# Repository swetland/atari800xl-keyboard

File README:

This is a work-in-progress replacement keyboard for the Atari800XL,
using Cherry MX mechanical key switches. 

- It is *not* entirely finished and production ready. 
- It has some clearance problems with the case top on the right hand side.  
- I do not have time to actively support it.

- Schematics and Layouts were done with KiCad 5.x

Parts Notes:
- A100254CT-ND (digikey) TE 2-84952-4 CONN FPC BOTTOM 24POS

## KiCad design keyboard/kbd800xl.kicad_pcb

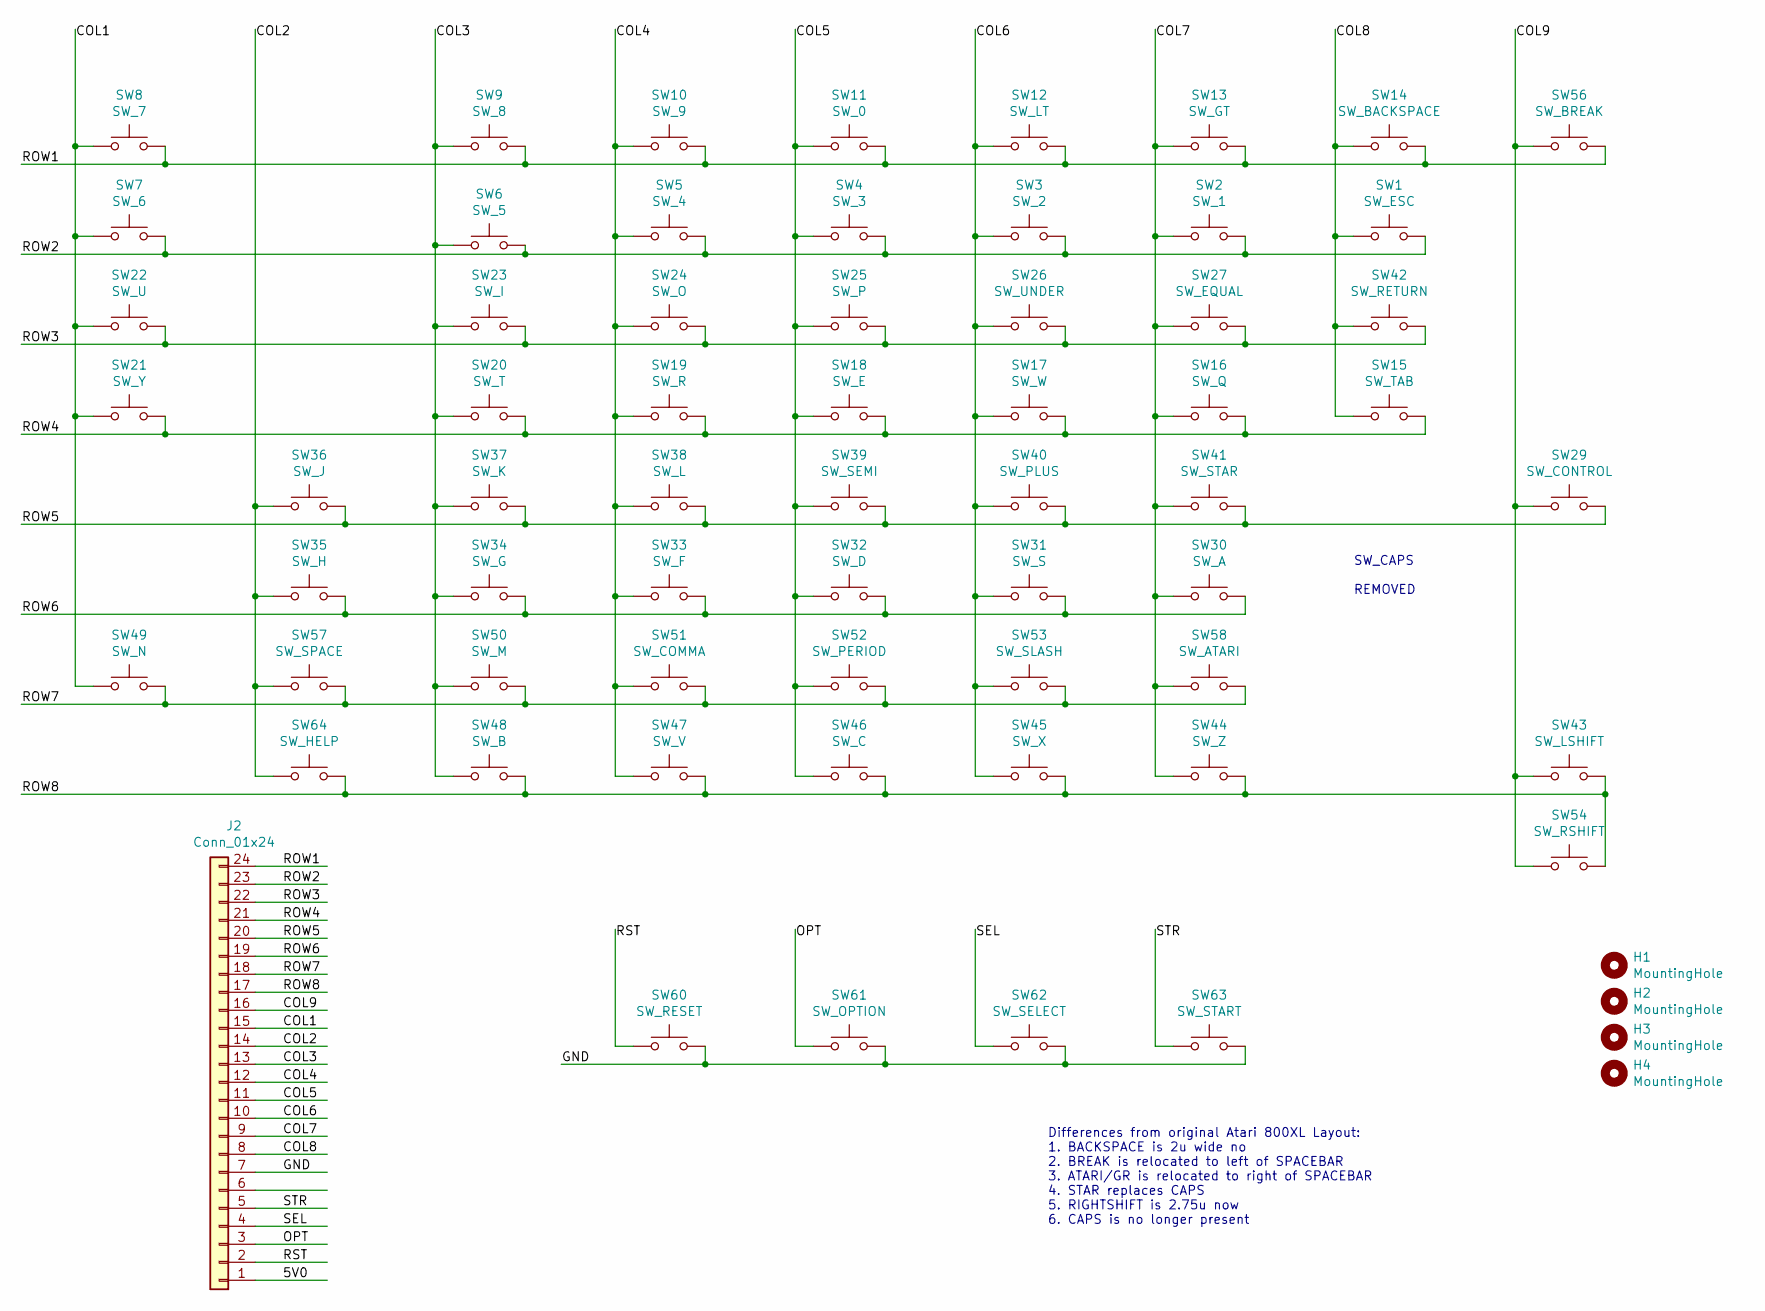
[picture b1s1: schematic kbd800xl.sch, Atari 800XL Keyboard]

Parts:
H1, H2, H3, H4: MountingHole; MountingHole_3mm
J2: Conn_01x24; TE_2-84952-4_1x24-1MP_P1.0mm_Horizontal
SW1: SW_ESC; SW_Cherry_MX_1.00u_PCB
SW2: SW_1; SW_Cherry_MX_1.00u_PCB
SW3: SW_2; SW_Cherry_MX_1.00u_PCB
SW4: SW_3; SW_Cherry_MX_1.00u_PCB
SW5: SW_4; SW_Cherry_MX_1.00u_PCB
SW6: SW_5; SW_Cherry_MX_1.00u_PCB
SW7: SW_6; SW_Cherry_MX_1.00u_PCB
SW8: SW_7; SW_Cherry_MX_1.00u_PCB
SW9: SW_8; SW_Cherry_MX_1.00u_PCB
SW10: SW_9; SW_Cherry_MX_1.00u_PCB
SW11: SW_0; SW_Cherry_MX_1.00u_PCB
SW12: SW_LT; SW_Cherry_MX_1.00u_PCB
SW13: SW_GT; SW_Cherry_MX_1.00u_PCB
SW14: SW_BACKSPACE; SW_Cherry_MX_2.00u_PCB
SW15: SW_TAB; SW_Cherry_MX_1.50u_PCB
SW16: SW_Q; SW_Cherry_MX_1.00u_PCB
SW17: SW_W; SW_Cherry_MX_1.00u_PCB
SW18: SW_E; SW_Cherry_MX_1.00u_PCB
SW19: SW_R; SW_Cherry_MX_1.00u_PCB
SW20: SW_T; SW_Cherry_MX_1.00u_PCB
SW21: SW_Y; SW_Cherry_MX_1.00u_PCB
SW22: SW_U; SW_Cherry_MX_1.00u_PCB
SW23: SW_I; SW_Cherry_MX_1.00u_PCB
SW24: SW_O; SW_Cherry_MX_1.00u_PCB
SW25: SW_P; SW_Cherry_MX_1.00u_PCB
SW26: SW_UNDER; SW_Cherry_MX_1.00u_PCB
SW27: SW_EQUAL; SW_Cherry_MX_1.00u_PCB
SW29: SW_CONTROL; SW_Cherry_MX_1.75u_PCB
SW30: SW_A; SW_Cherry_MX_1.00u_PCB
SW31: SW_S; SW_Cherry_MX_1.00u_PCB
SW32: SW_D; SW_Cherry_MX_1.00u_PCB
SW33: SW_F; SW_Cherry_MX_1.00u_PCB
SW34: SW_G; SW_Cherry_MX_1.00u_PCB
SW35: SW_H; SW_Cherry_MX_1.00u_PCB
SW36: SW_J; SW_Cherry_MX_1.00u_PCB
SW37: SW_K; SW_Cherry_MX_1.00u_PCB
SW38: SW_L; SW_Cherry_MX_1.00u_PCB
SW39: SW_SEMI; SW_Cherry_MX_1.00u_PCB
SW40: SW_PLUS; SW_Cherry_MX_1.00u_PCB
SW41: SW_STAR; SW_Cherry_MX_1.50u_PCB
SW42: SW_RETURN; SW_Cherry_MX_2.25u_PCB
SW43: SW_LSHIFT; SW_Cherry_MX_2.25u_PCB
SW44: SW_Z; SW_Cherry_MX_1.00u_PCB
SW45: SW_X; SW_Cherry_MX_1.00u_PCB
SW46: SW_C; SW_Cherry_MX_1.00u_PCB
SW47: SW_V; SW_Cherry_MX_1.00u_PCB
SW48: SW_B; SW_Cherry_MX_1.00u_PCB
SW49: SW_N; SW_Cherry_MX_1.00u_PCB
SW50: SW_M; SW_Cherry_MX_1.00u_PCB
SW51: SW_COMMA; SW_Cherry_MX_1.00u_PCB
SW52: SW_PERIOD; SW_Cherry_MX_1.00u_PCB
SW53: SW_SLASH; SW_Cherry_MX_1.00u_PCB
SW54: SW_RSHIFT; SW_Cherry_MX_2.75u_PCB
SW56: SW_BREAK; SW_Cherry_MX_1.25u_PCB
SW57: SW_SPACE; SW_Cherry_MX_6.25u_PCB
SW58: SW_ATARI; SW_Cherry_MX_1.25u_PCB
SW60: SW_RESET; SW_Cherry_MX_1.00u_PCB
SW61: SW_OPTION; SW_Cherry_MX_1.00u_PCB
SW62: SW_SELECT; SW_Cherry_MX_1.00u_PCB
SW63: SW_START; SW_Cherry_MX_1.00u_PCB
SW64: SW_HELP; SW_Cherry_MX_1.00u_PCB

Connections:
/5V0: J2.1
/COL1: J2.15, SW7.1, SW8.1, SW21.1, SW22.1, SW49.1
/COL2: J2.14, SW35.1, SW36.1, SW57.1, SW64.1
/COL3: J2.13, SW6.1, SW9.1, SW20.1, SW23.1, SW34.1, SW37.1, SW48.1, SW50.1
/COL4: J2.12, SW5.1, SW10.1, SW19.1, SW24.1, SW33.1, SW38.1, SW47.1, SW51.1
/COL5: J2.11, SW4.1, SW11.1, SW18.1, SW25.1, SW32.1, SW39.1, SW46.1, SW52.1
/COL6: J2.10, SW3.1, SW12.1, SW17.1, SW26.1, SW31.1, SW40.1, SW45.1, SW53.1
/COL7: J2.9, SW2.1, SW13.1, SW16.1, SW27.1, SW30.1, SW41.1, SW44.1, SW58.1
/COL8: J2.8, SW1.1, SW14.1, SW15.1, SW42.1
/COL9: J2.16, SW29.1, SW43.1, SW54.1, SW56.1
/GND: J2.7, SW60.2, SW61.2, SW62.2, SW63.2
/OPT: J2.3, SW61.1
/ROW1: J2.24, SW8.2, SW9.2, SW10.2, SW11.2, SW12.2, SW13.2, SW14.2, SW56.2
/ROW2: J2.23, SW1.2, SW2.2, SW3.2, SW4.2, SW5.2, SW6.2, SW7.2
/ROW3: J2.22, SW22.2, SW23.2, SW24.2, SW25.2, SW26.2, SW27.2, SW42.2
/ROW4: J2.21, SW15.2, SW16.2, SW17.2, SW18.2, SW19.2, SW20.2, SW21.2
/ROW5: J2.20, SW29.2, SW36.2, SW37.2, SW38.2, SW39.2, SW40.2, SW41.2
/ROW6: J2.19, SW30.2, SW31.2, SW32.2, SW33.2, SW34.2, SW35.2
/ROW7: J2.18, SW49.2, SW50.2, SW51.2, SW52.2, SW53.2, SW57.2, SW58.2
/ROW8: J2.17, SW43.2, SW44.2, SW45.2, SW46.2, SW47.2, SW48.2, SW54.2, SW64.2
/RST: J2.2, SW60.1
/SEL: J2.4, SW62.1
/STR: J2.5, SW63.1

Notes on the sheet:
Differences from original Atari 800XL Layout: 1. BACKSPACE is 2u wide no 2. BREAK is relocated to left of SPACEBAR 3. ATARI/GR is relocated to right of SPACEBAR 4. STAR replaces CAPS 5. RIGHTSHIFT is 2.75u now 6. CAPS is no longer present
SW_CAPS REMOVED

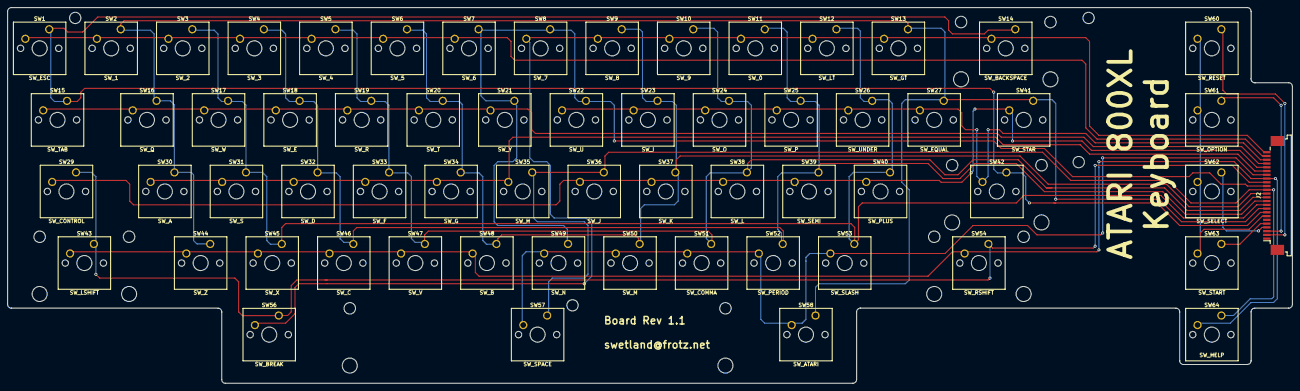
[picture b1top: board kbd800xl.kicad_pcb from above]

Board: 2 copper layers, 342.0 x 100.0 mm, 66 parts (0 on the bottom side), 22 nets.

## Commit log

2020-10-20 initial checkin of keyboard kicad project
2020-10-20 initial checkin of flex connector kicad project
2020-10-20 readme and license
2021-01-22 keycap layouts
2021-01-22 some pictures
2021-02-16 add picture to readme
2021-02-16 readme: markdown
